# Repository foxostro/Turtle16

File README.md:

# Turtle16

Turtle16 is a sixteen-bit microcomputer built from discrete logic ICs and other simple parts. This repo contains the Kicad project, and other files necesary to build the hardware, as well as the simulator, assembler, and compiler.

## Computer Specifications

* Sixteen-bit homebrew CPU
* Five stage classic RISC pipeline, executing one instruction per clock cycle
* Eight general-purpose registers
* Operand forwarding to automatically resolve read-after-write hazards
* Pipeline stalls to automatically resolve other sorts of hazards
* No branch delay slots
* Primitive branch prediction, always predicting the branch is not taken

## Why did you do this?

I find computer architecture to be very interesting. Having already built a couple of homebrew breadboard computers in the style of the SAP-1, I wanted to do something more advanced. This an opportunity to learn how the classic five stage RISC pipeline works. While it would also be possible to build something like this in an FPGA, or even just an HDL simulator, I appreciate the physical reality of building an actual thing. At the same time, I've been learning so much about PCB layout, circuit design, circuit assembly and construction, and debugging, much of which seems broadly applicable to any electronics project.

Careful self-imposed limitations are important for a successful project. Limitation breeds creativity. For this project, the implementation of the CPU itself has been constrained to use only simple 7400-style parts. This means sticking to discrete logic and other medium-scale integration parts. Microprocessors and advanced FPGAs have been avoided. An exception has been made for primitive GALs as these fit the retro computer aesthetic.

For the computer's peripherals, I might relax these limitations in favor of getting something working. For example, I'm considering using an Arduino to interface with a PC. The sound hardware could be built around a retro-style audio IC such as one of the Yamaha OPL series chips or the Phillips SAA1099.

The danger of relaxing limitations is that it raises the question, why not go further? If I decide it's fine to implement graphics using a retro-style chip like the TMS9918A then why not use a Raspberry Pi, or the Gameduino 3X Dazzler? Why not simply implement the entire computer in an emulator running on a Raspberry Pi? Once placed in an enclosure, it won't look any different. The answer is that the project is not about the goal of building a working computer, or the goal of playing some games. This project is centered around learning how computers work.

## Getting Started

The simulator app can be used to simulate the computer and run example programs without having to build the hardware. The interactive debugger can be used to inspect the state of the computer. Several example saved simulator sessions are available in the TurtleTools/Examples/ directory. (At some point, I should add some better demoes. These are mostly just programs that I used in hardware verification.)

To run the simulator, open the TurtleTools Xcode project and run the Simulator16 scheme. Refer to the [Tool Chain](Documentation/TurtleTools.md) page for more details.

## Documentation

* [Architecture Overview](Documentation/Architecture.md)
* [Instruction Set Architecture](Documentation/ISA.md)
* [Programming](Documentation/Programming.md)
* [Tool Chain](Documentation/TurtleTools.md)
* [Bugs](Documentation/Bugs.md)
* [Future Work](Documentation/Future.md)

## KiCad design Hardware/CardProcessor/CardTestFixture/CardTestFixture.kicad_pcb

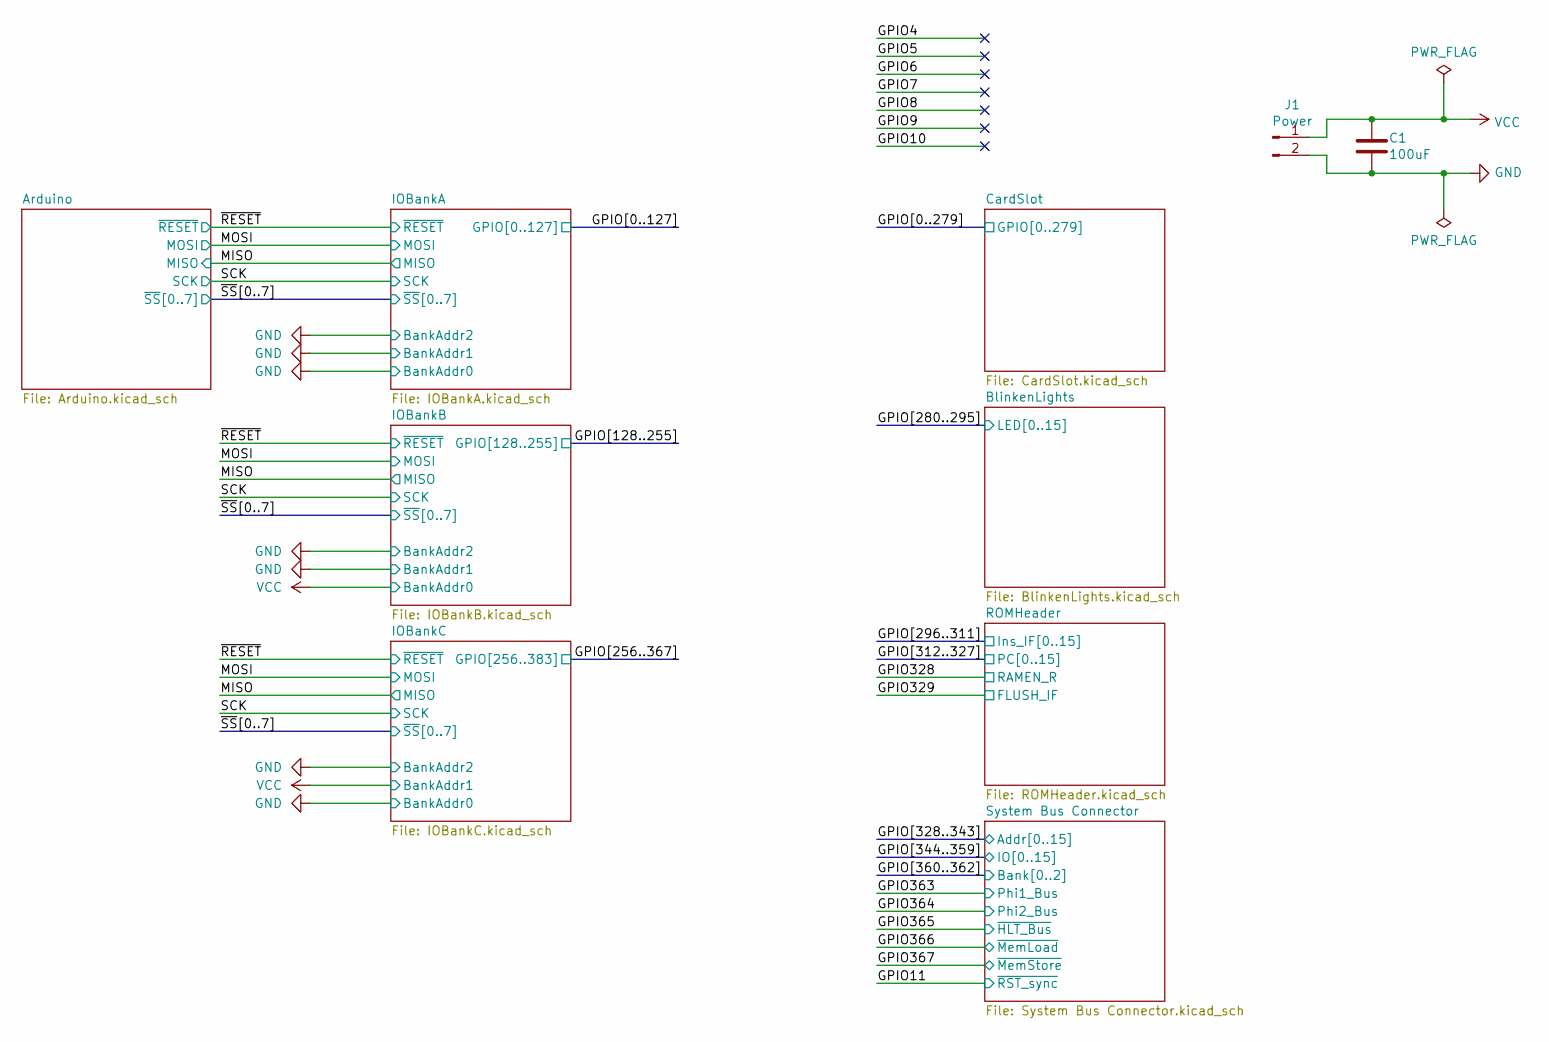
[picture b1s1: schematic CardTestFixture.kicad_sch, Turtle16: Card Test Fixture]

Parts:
C1: 100uF; C_1206_3216Metric; Manufacturer# AMK316ABJ107ML-T; Mouser# 963-AMK316ABJ107ML-T
J1: Power; 172448-0002; Manufacturer# 172448-0002; Mouser# 538-172448-0002

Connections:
GND: C1.2, J1.2; also elsewhere on the board
VCC: C1.1, J1.1; also elsewhere on the board

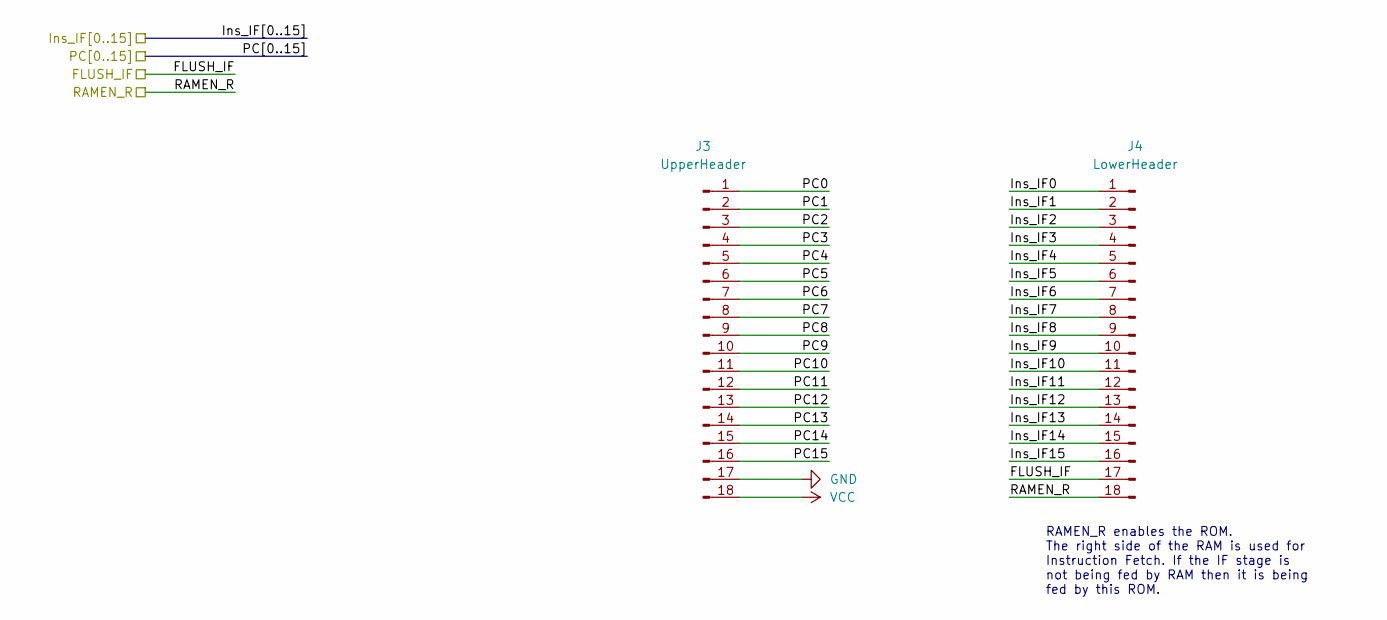
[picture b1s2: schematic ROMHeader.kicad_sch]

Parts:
J3: UpperHeader; PinHeader_1x18_P2.54mm_Vertical
J4: LowerHeader; PinHeader_1x18_P2.54mm_Vertical

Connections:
/GPIO296: J4.1; also elsewhere on the board
/GPIO297: J4.2; also elsewhere on the board
/GPIO298: J4.3; also elsewhere on the board
/GPIO299: J4.4; also elsewhere on the board
/GPIO300: J4.5; also elsewhere on the board
/GPIO301: J4.6; also elsewhere on the board
/GPIO302: J4.7; also elsewhere on the board
/GPIO303: J4.8; also elsewhere on the board
/GPIO304: J4.9; also elsewhere on the board
/GPIO305: J4.10; also elsewhere on the board
/GPIO306: J4.11; also elsewhere on the board
/GPIO307: J4.12; also elsewhere on the board
/GPIO308: J4.13; also elsewhere on the board
/GPIO309: J4.14; also elsewhere on the board
/GPIO310: J4.15; also elsewhere on the board
/GPIO311: J4.16; also elsewhere on the board
/GPIO312: J3.1; also elsewhere on the board
/GPIO313: J3.2; also elsewhere on the board
/GPIO314: J3.3; also elsewhere on the board
/GPIO315: J3.4; also elsewhere on the board
/GPIO316: J3.5; also elsewhere on the board
/GPIO317: J3.6; also elsewhere on the board
/GPIO318: J3.7; also elsewhere on the board
/GPIO319: J3.8; also elsewhere on the board
/GPIO320: J3.9; also elsewhere on the board
/GPIO321: J3.10; also elsewhere on the board
/GPIO322: J3.11; also elsewhere on the board
/GPIO323: J3.12; also elsewhere on the board
/GPIO324: J3.13; also elsewhere on the board
/GPIO325: J3.14; also elsewhere on the board
/GPIO326: J3.15; also elsewhere on the board
/GPIO327: J3.16; also elsewhere on the board
/GPIO328: J4.18; also elsewhere on the board
/GPIO329: J4.17; also elsewhere on the board
GND: J3.17; also elsewhere on the board
VCC: J3.18; also elsewhere on the board

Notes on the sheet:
RAMEN_R enables the ROM. The right side of the RAM is used for Instruction Fetch. If the IF stage is not being fed by RAM then it is being fed by this ROM.

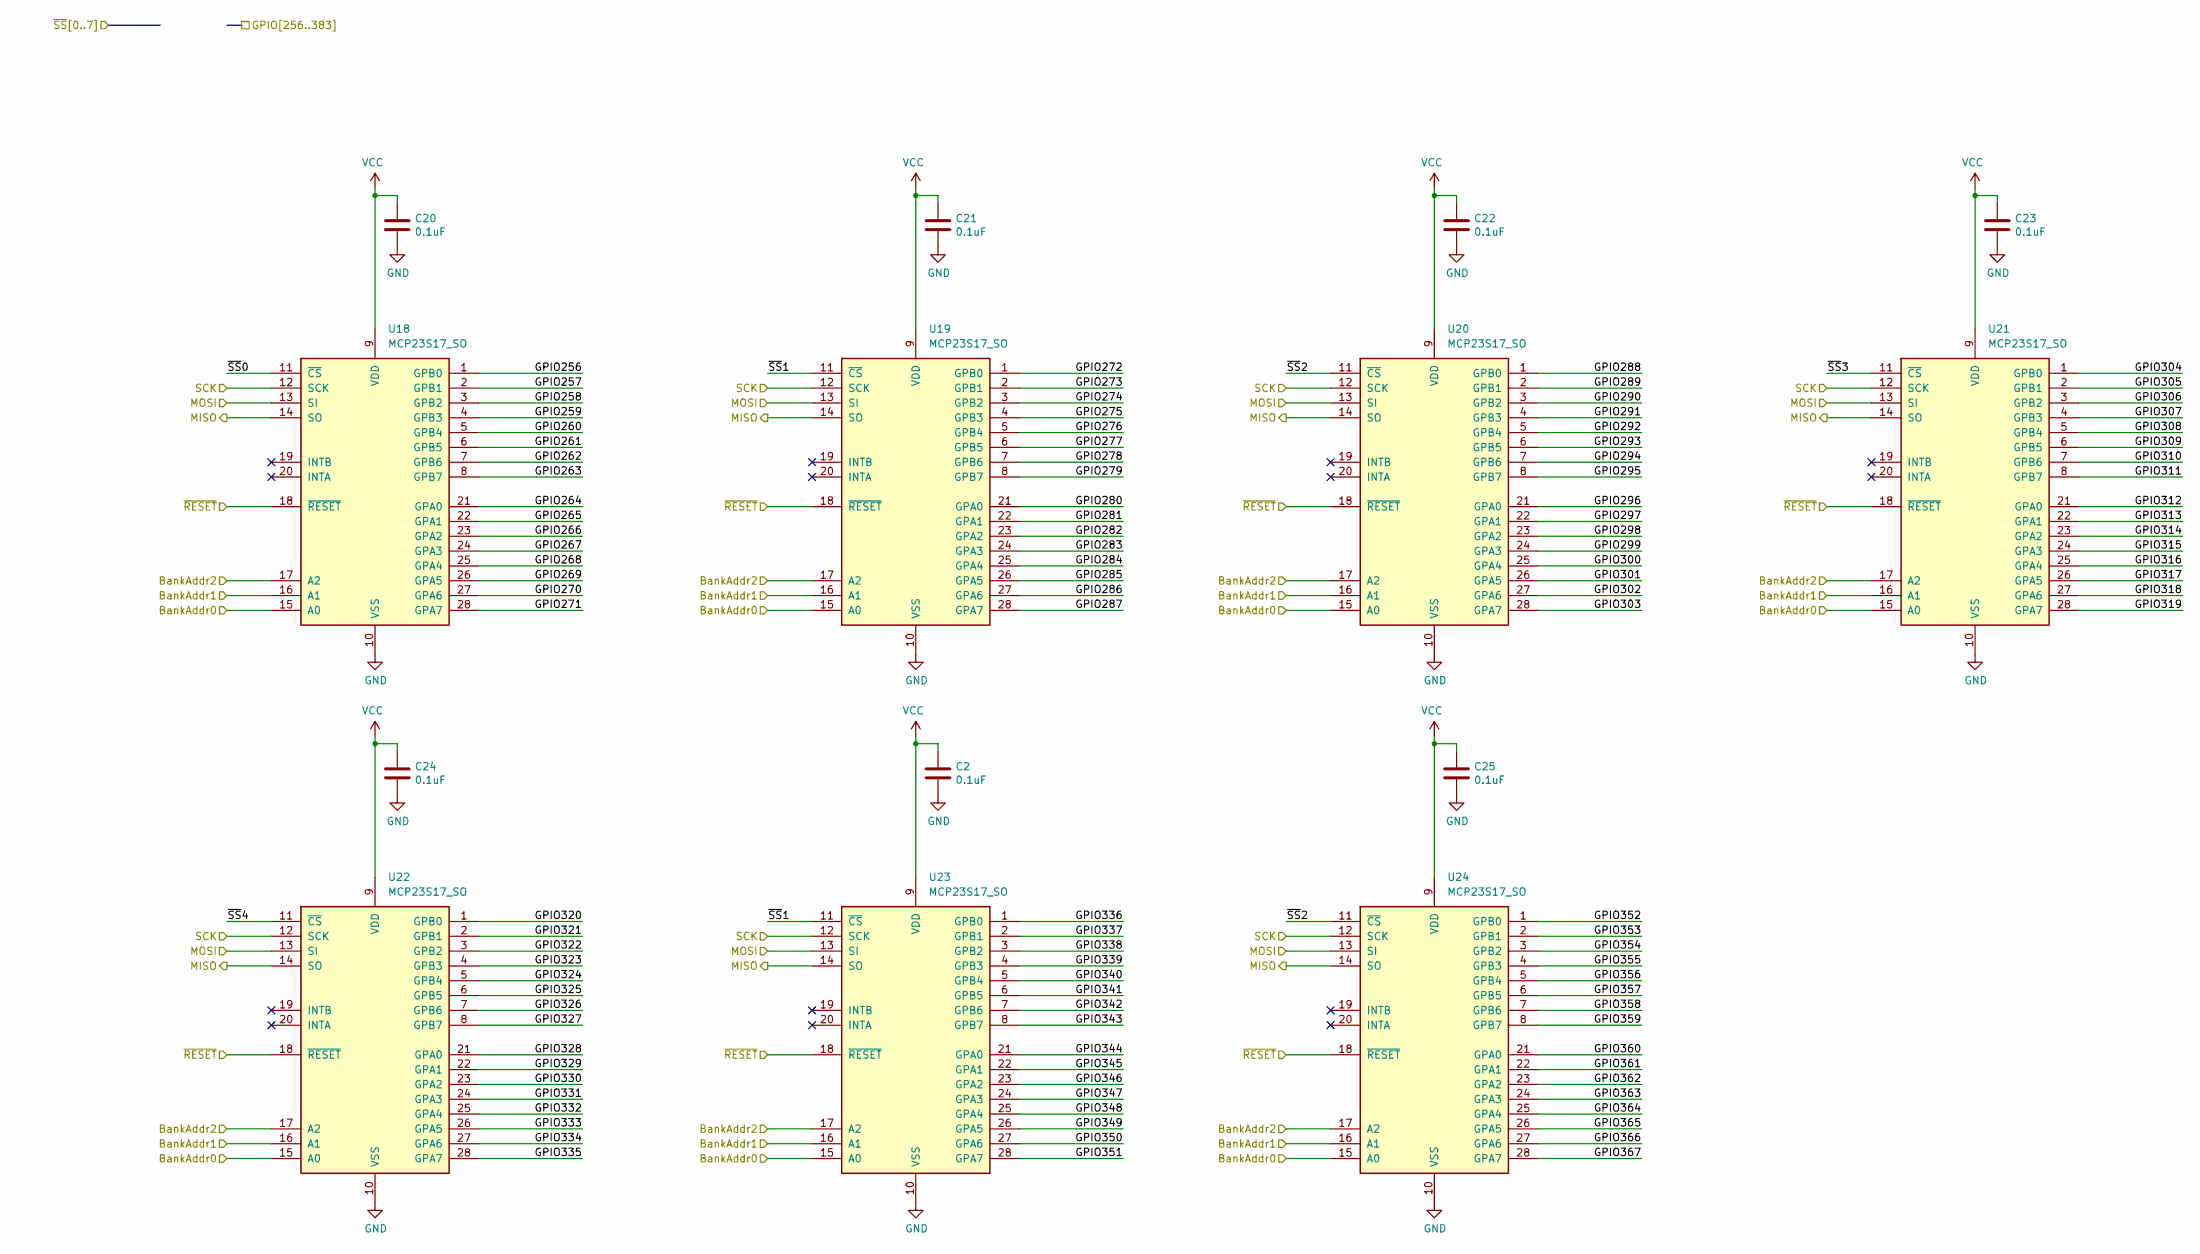
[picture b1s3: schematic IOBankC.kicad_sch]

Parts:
C2, C20, C21, C22, C23, C24, C25: 0.1uF; C_0603_1608Metric; Manufacturer# EMK107B7104KAHT; Mouser# 963-EMK107B7104KAHT
U18, U19, U20, U21, U22, U23, U24: MCP23S17_SO; SOIC-28W_7.5x17.9mm_P1.27mm

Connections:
/GPIO256: U18.1 (GPB0); also elsewhere on the board
/GPIO257: U18.2 (GPB1); also elsewhere on the board
/GPIO258: U18.3 (GPB2); also elsewhere on the board
/GPIO259: U18.4 (GPB3); also elsewhere on the board
/GPIO260: U18.5 (GPB4); also elsewhere on the board
/GPIO261: U18.6 (GPB5); also elsewhere on the board
/GPIO262: U18.7 (GPB6); also elsewhere on the board
/GPIO263: U18.8 (GPB7); also elsewhere on the board
/GPIO264: U18.21 (GPA0); also elsewhere on the board
/GPIO265: U18.22 (GPA1); also elsewhere on the board
/GPIO266: U18.23 (GPA2); also elsewhere on the board
/GPIO267: U18.24 (GPA3); also elsewhere on the board
/GPIO268: U18.25 (GPA4); also elsewhere on the board
/GPIO269: U18.26 (GPA5); also elsewhere on the board
/GPIO270: U18.27 (GPA6); also elsewhere on the board
/GPIO271: U18.28 (GPA7); also elsewhere on the board
/GPIO272: U19.1 (GPB0); also elsewhere on the board
/GPIO273: U19.2 (GPB1); also elsewhere on the board
/GPIO274: U19.3 (GPB2); also elsewhere on the board
/GPIO275: U19.4 (GPB3); also elsewhere on the board
/GPIO276: U19.5 (GPB4); also elsewhere on the board
/GPIO277: U19.6 (GPB5); also elsewhere on the board
/GPIO278: U19.7 (GPB6); also elsewhere on the board
/GPIO279: U19.8 (GPB7); also elsewhere on the board
/GPIO280: U19.21 (GPA0); also elsewhere on the board
/GPIO281: U19.22 (GPA1); also elsewhere on the board
/GPIO282: U19.23 (GPA2); also elsewhere on the board
/GPIO283: U19.24 (GPA3); also elsewhere on the board
/GPIO284: U19.25 (GPA4); also elsewhere on the board
/GPIO285: U19.26 (GPA5); also elsewhere on the board
/GPIO286: U19.27 (GPA6); also elsewhere on the board
/GPIO287: U19.28 (GPA7); also elsewhere on the board
/GPIO288: U20.1 (GPB0); also elsewhere on the board
/GPIO289: U20.2 (GPB1); also elsewhere on the board
/GPIO290: U20.3 (GPB2); also elsewhere on the board
/GPIO291: U20.4 (GPB3); also elsewhere on the board
/GPIO292: U20.5 (GPB4); also elsewhere on the board
/GPIO293: U20.6 (GPB5); also elsewhere on the board
/GPIO294: U20.7 (GPB6); also elsewhere on the board
/GPIO295: U20.8 (GPB7); also elsewhere on the board
/GPIO296: U20.21 (GPA0); also elsewhere on the board
/GPIO297: U20.22 (GPA1); also elsewhere on the board
/GPIO298: U20.23 (GPA2); also elsewhere on the board
/GPIO299: U20.24 (GPA3); also elsewhere on the board
/GPIO300: U20.25 (GPA4); also elsewhere on the board
/GPIO301: U20.26 (GPA5); also elsewhere on the board
/GPIO302: U20.27 (GPA6); also elsewhere on the board
/GPIO303: U20.28 (GPA7); also elsewhere on the board
/GPIO304: U21.1 (GPB0); also elsewhere on the board
/GPIO305: U21.2 (GPB1); also elsewhere on the board
/GPIO306: U21.3 (GPB2); also elsewhere on the board
/GPIO307: U21.4 (GPB3); also elsewhere on the board
/GPIO308: U21.5 (GPB4); also elsewhere on the board
/GPIO309: U21.6 (GPB5); also elsewhere on the board
/GPIO310: U21.7 (GPB6); also elsewhere on the board
/GPIO311: U21.8 (GPB7); also elsewhere on the board
/GPIO312: U21.21 (GPA0); also elsewhere on the board
/GPIO313: U21.22 (GPA1); also elsewhere on the board
/GPIO314: U21.23 (GPA2); also elsewhere on the board
/GPIO315: U21.24 (GPA3); also elsewhere on the board
/GPIO316: U21.25 (GPA4); also elsewhere on the board
/GPIO317: U21.26 (GPA5); also elsewhere on the board
/GPIO318: U21.27 (GPA6); also elsewhere on the board
/GPIO319: U21.28 (GPA7); also elsewhere on the board
/GPIO320: U22.1 (GPB0); also elsewhere on the board
/GPIO321: U22.2 (GPB1); also elsewhere on the board
/GPIO322: U22.3 (GPB2); also elsewhere on the board
/GPIO323: U22.4 (GPB3); also elsewhere on the board
/GPIO324: U22.5 (GPB4); also elsewhere on the board
/GPIO325: U22.6 (GPB5); also elsewhere on the board
/GPIO326: U22.7 (GPB6); also elsewhere on the board
/GPIO327: U22.8 (GPB7); also elsewhere on the board
/GPIO328: U22.21 (GPA0); also elsewhere on the board
/GPIO329: U22.22 (GPA1); also elsewhere on the board
/GPIO330: U22.23 (GPA2); also elsewhere on the board
/GPIO331: U22.24 (GPA3); also elsewhere on the board
/GPIO332: U22.25 (GPA4); also elsewhere on the board
/GPIO333: U22.26 (GPA5); also elsewhere on the board
/GPIO334: U22.27 (GPA6); also elsewhere on the board
/GPIO335: U22.28 (GPA7); also elsewhere on the board
/GPIO336: U23.1 (GPB0); also elsewhere on the board
/GPIO337: U23.2 (GPB1); also elsewhere on the board
/GPIO338: U23.3 (GPB2); also elsewhere on the board
/GPIO339: U23.4 (GPB3); also elsewhere on the board
/GPIO340: U23.5 (GPB4); also elsewhere on the board
/GPIO341: U23.6 (GPB5); also elsewhere on the board
/GPIO342: U23.7 (GPB6); also elsewhere on the board
/GPIO343: U23.8 (GPB7); also elsewhere on the board
/GPIO344: U23.21 (GPA0); also elsewhere on the board
/GPIO345: U23.22 (GPA1); also elsewhere on the board
/GPIO346: U23.23 (GPA2); also elsewhere on the board
/GPIO347: U23.24 (GPA3); also elsewhere on the board
/GPIO348: U23.25 (GPA4); also elsewhere on the board
/GPIO349: U23.26 (GPA5); also elsewhere on the board
/GPIO350: U23.27 (GPA6); also elsewhere on the board
/GPIO351: U23.28 (GPA7); also elsewhere on the board
/GPIO352: U24.1 (GPB0); also elsewhere on the board
/GPIO353: U24.2 (GPB1); also elsewhere on the board
/GPIO354: U24.3 (GPB2); also elsewhere on the board
/GPIO355: U24.4 (GPB3); also elsewhere on the board
/GPIO356: U24.5 (GPB4); also elsewhere on the board
/GPIO357: U24.6 (GPB5); also elsewhere on the board
/GPIO358: U24.7 (GPB6); also elsewhere on the board
/GPIO359: U24.8 (GPB7); also elsewhere on the board
/GPIO360: U24.21 (GPA0); also elsewhere on the board
/GPIO361: U24.22 (GPA1); also elsewhere on the board
/GPIO362: U24.23 (GPA2); also elsewhere on the board
/GPIO363: U24.24 (GPA3); also elsewhere on the board
/GPIO364: U24.25 (GPA4); also elsewhere on the board
/GPIO365: U24.26 (GPA5); also elsewhere on the board
/GPIO366: U24.27 (GPA6); also elsewhere on the board
/GPIO367: U24.28 (GPA7); also elsewhere on the board
/MISO: U18.14 (SO), U19.14 (SO), U20.14 (SO), U21.14 (SO), U22.14 (SO), U23.14 (SO), U24.14 (SO); also elsewhere on the board
/MOSI: U18.13 (SI), U19.13 (SI), U20.13 (SI), U21.13 (SI), U22.13 (SI), U23.13 (SI), U24.13 (SI); also elsewhere on the board
/SCK: U18.12 (SCK), U19.12 (SCK), U20.12 (SCK), U21.12 (SCK), U22.12 (SCK), U23.12 (SCK), U24.12 (SCK); also elsewhere on the board
/~RESET: U18.18 (~RESET), U19.18 (~RESET), U20.18 (~RESET), U21.18 (~RESET), U22.18 (~RESET), U23.18 (~RESET), U24.18 (~RESET); also elsewhere on the board
/~SS0: U18.11 (~CS); also elsewhere on the board
/~SS1: U19.11 (~CS), U23.11 (~CS); also elsewhere on the board
/~SS2: U20.11 (~CS), U24.11 (~CS); also elsewhere on the board
/~SS3: U21.11 (~CS); also elsewhere on the board
/~SS4: U22.11 (~CS); also elsewhere on the board
GND: C2.2, C20.2, C21.2, C22.2, C23.2, C24.2, C25.2, U18.10 (VSS), U18.15 (A0), U18.17 (A2), U19.10 (VSS), U19.15 (A0), U19.17 (A2), U20.10 (VSS), U20.15 (A0), U20.17 (A2), U21.10 (VSS), U21.15 (A0), U21.17 (A2), U22.10 (VSS), U22.15 (A0), U22.17 (A2), U23.10 (VSS), U23.15 (A0), U23.17 (A2), U24.10 (VSS), U24.15 (A0), U24.17 (A2); also elsewhere on the board
VCC: C2.1, C20.1, C21.1, C22.1, C23.1, C24.1, C25.1, U18.9 (VDD), U18.16 (A1), U19.9 (VDD), U19.16 (A1), U20.9 (VDD), U20.16 (A1), U21.9 (VDD), U21.16 (A1), U22.9 (VDD), U22.16 (A1), U23.9 (VDD), U23.16 (A1), U24.9 (VDD), U24.16 (A1); also elsewhere on the board

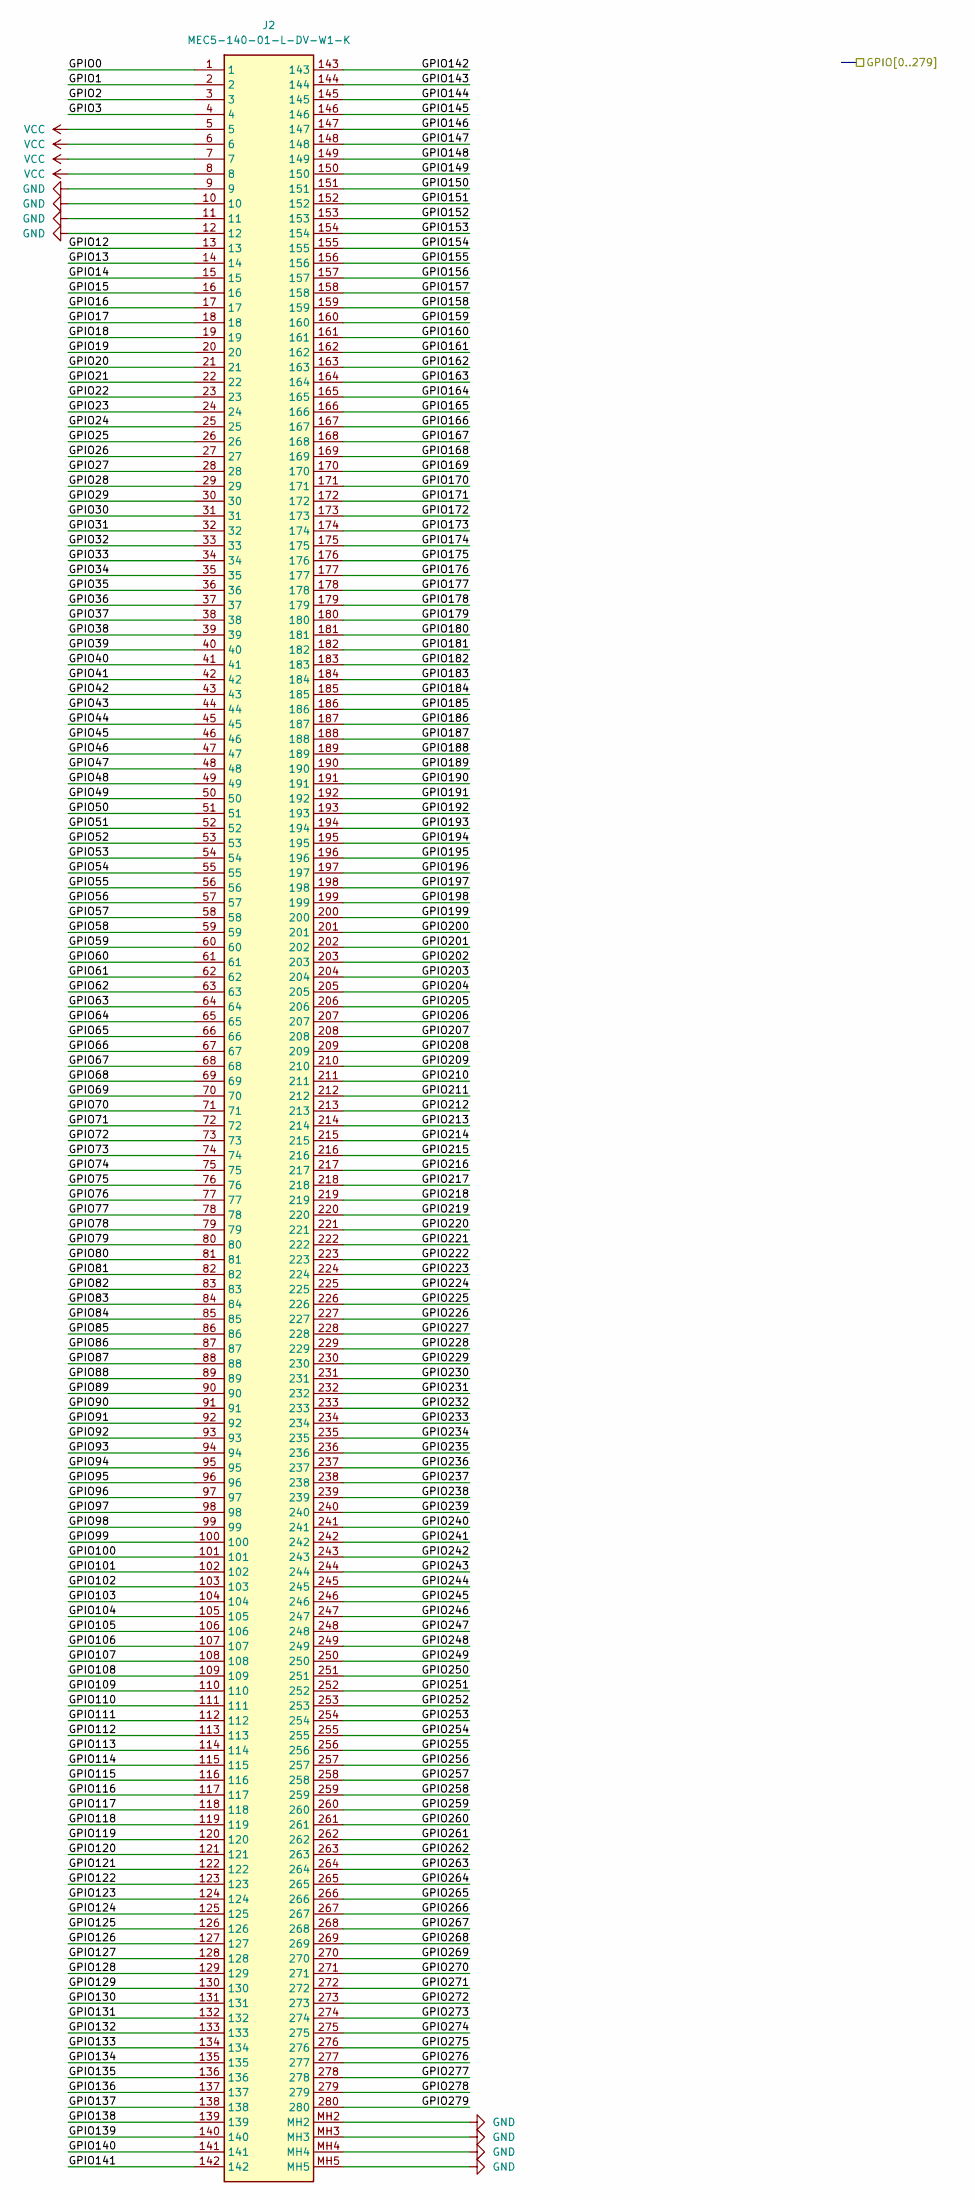
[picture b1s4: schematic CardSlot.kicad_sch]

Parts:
J2: MEC5-140-01-L-DV-W1-K; MEC514001LDVW1K; Mouser Part Number 200-MEC514001LDVW1K

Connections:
/GPIO0: J2.1; also elsewhere on the board
/GPIO1: J2.2; also elsewhere on the board
/GPIO2: J2.3; also elsewhere on the board
/GPIO3: J2.4; also elsewhere on the board
/GPIO12: J2.13; also elsewhere on the board
/GPIO13: J2.14; also elsewhere on the board
/GPIO14: J2.15; also elsewhere on the board
/GPIO15: J2.16; also elsewhere on the board
/GPIO16: J2.17; also elsewhere on the board
/GPIO17: J2.18; also elsewhere on the board
/GPIO18: J2.19; also elsewhere on the board
/GPIO19: J2.20; also elsewhere on the board
/GPIO20: J2.21; also elsewhere on the board
/GPIO21: J2.22; also elsewhere on the board
/GPIO22: J2.23; also elsewhere on the board
/GPIO23: J2.24; also elsewhere on the board
/GPIO24: J2.25; also elsewhere on the board
/GPIO25: J2.26; also elsewhere on the board
/GPIO26: J2.27; also elsewhere on the board
/GPIO27: J2.28; also elsewhere on the board
/GPIO28: J2.29; also elsewhere on the board
/GPIO29: J2.30; also elsewhere on the board
/GPIO30: J2.31; also elsewhere on the board
/GPIO31: J2.32; also elsewhere on the board
/GPIO32: J2.33; also elsewhere on the board
/GPIO33: J2.34; also elsewhere on the board
/GPIO34: J2.35; also elsewhere on the board
/GPIO35: J2.36; also elsewhere on the board
/GPIO36: J2.37; also elsewhere on the board
/GPIO37: J2.38; also elsewhere on the board
/GPIO38: J2.39; also elsewhere on the board
/GPIO39: J2.40; also elsewhere on the board
/GPIO40: J2.41; also elsewhere on the board
/GPIO41: J2.42; also elsewhere on the board
/GPIO42: J2.43; also elsewhere on the board
/GPIO43: J2.44; also elsewhere on the board
/GPIO44: J2.45; also elsewhere on the board
/GPIO45: J2.46; also elsewhere on the board
/GPIO46: J2.47; also elsewhere on the board
/GPIO47: J2.48; also elsewhere on the board
/GPIO48: J2.49; also elsewhere on the board
/GPIO49: J2.50; also elsewhere on the board
/GPIO50: J2.51; also elsewhere on the board
/GPIO51: J2.52; also elsewhere on the board
/GPIO52: J2.53; also elsewhere on the board
/GPIO53: J2.54; also elsewhere on the board
/GPIO54: J2.55; also elsewhere on the board
/GPIO55: J2.56; also elsewhere on the board
/GPIO56: J2.57; also elsewhere on the board
/GPIO57: J2.58; also elsewhere on the board
/GPIO58: J2.59; also elsewhere on the board
/GPIO59: J2.60; also elsewhere on the board
/GPIO60: J2.61; also elsewhere on the board
/GPIO61: J2.62; also elsewhere on the board
/GPIO62: J2.63; also elsewhere on the board
/GPIO63: J2.64; also elsewhere on the board
/GPIO64: J2.65; also elsewhere on the board
/GPIO65: J2.66; also elsewhere on the board
/GPIO66: J2.67; also elsewhere on the board
/GPIO67: J2.68; also elsewhere on the board
/GPIO68: J2.69; also elsewhere on the board
/GPIO69: J2.70; also elsewhere on the board
/GPIO70: J2.71; also elsewhere on the board
/GPIO71: J2.72; also elsewhere on the board
/GPIO72: J2.73; also elsewhere on the board
/GPIO73: J2.74; also elsewhere on the board
/GPIO74: J2.75; also elsewhere on the board
/GPIO75: J2.76; also elsewhere on the board
/GPIO76: J2.77; also elsewhere on the board
/GPIO77: J2.78; also elsewhere on the board
/GPIO78: J2.79; also elsewhere on the board
/GPIO79: J2.80; also elsewhere on the board
/GPIO80: J2.81; also elsewhere on the board
/GPIO81: J2.82; also elsewhere on the board
/GPIO82: J2.83; also elsewhere on the board
/GPIO83: J2.84; also elsewhere on the board
/GPIO84: J2.85; also elsewhere on the board
/GPIO85: J2.86; also elsewhere on the board
/GPIO86: J2.87; also elsewhere on the board
/GPIO87: J2.88; also elsewhere on the board
/GPIO88: J2.89; also elsewhere on the board
/GPIO89: J2.90; also elsewhere on the board
/GPIO90: J2.91; also elsewhere on the board
/GPIO91: J2.92; also elsewhere on the board
/GPIO92: J2.93; also elsewhere on the board
/GPIO93: J2.94; also elsewhere on the board
/GPIO94: J2.95; also elsewhere on the board
/GPIO95: J2.96; also elsewhere on the board
/GPIO96: J2.97; also elsewhere on the board
/GPIO97: J2.98; also elsewhere on the board
/GPIO98: J2.99; also elsewhere on the board
/GPIO99: J2.100; also elsewhere on the board
/GPIO100: J2.101; also elsewhere on the board
/GPIO101: J2.102; also elsewhere on the board
/GPIO102: J2.103; also elsewhere on the board
/GPIO103: J2.104; also elsewhere on the board
/GPIO104: J2.105; also elsewhere on the board
/GPIO105: J2.106; also elsewhere on the board
/GPIO106: J2.107; also elsewhere on the board
/GPIO107: J2.108; also elsewhere on the board
/GPIO108: J2.109; also elsewhere on the board
/GPIO109: J2.110; also elsewhere on the board
/GPIO110: J2.111; also elsewhere on the board
/GPIO111: J2.112; also elsewhere on the board
/GPIO112: J2.113; also elsewhere on the board
/GPIO113: J2.114; also elsewhere on the board
/GPIO114: J2.115; also elsewhere on the board
/GPIO115: J2.116; also elsewhere on the board
/GPIO116: J2.117; also elsewhere on the board
/GPIO117: J2.118; also elsewhere on the board
/GPIO118: J2.119; also elsewhere on the board
/GPIO119: J2.120; also elsewhere on the board
/GPIO120: J2.121; also elsewhere on the board
/GPIO121: J2.122; also elsewhere on the board
/GPIO122: J2.123; also elsewhere on the board
/GPIO123: J2.124; also elsewhere on the board
/GPIO124: J2.125; also elsewhere on the board
/GPIO125: J2.126; also elsewhere on the board
/GPIO126: J2.127; also elsewhere on the board
/GPIO127: J2.128; also elsewhere on the board
/GPIO128: J2.129; also elsewhere on the board
/GPIO129: J2.130; also elsewhere on the board
/GPIO130: J2.131; also elsewhere on the board
/GPIO131: J2.132; also elsewhere on the board
/GPIO132: J2.133; also elsewhere on the board
/GPIO133: J2.134; also elsewhere on the board
/GPIO134: J2.135; also elsewhere on the board
/GPIO135: J2.136; also elsewhere on the board
/GPIO136: J2.137; also elsewhere on the board
/GPIO137: J2.138; also elsewhere on the board
/GPIO138: J2.139; also elsewhere on the board
/GPIO139: J2.140; also elsewhere on the board
/GPIO140: J2.141; also elsewhere on the board
/GPIO141: J2.142; also elsewhere on the board
/GPIO142: J2.143; also elsewhere on the board
/GPIO143: J2.144; also elsewhere on the board
/GPIO144: J2.145; also elsewhere on the board
/GPIO145: J2.146; also elsewhere on the board
/GPIO146: J2.147; also elsewhere on the board
/GPIO147: J2.148; also elsewhere on the board
/GPIO148: J2.149; also elsewhere on the board
/GPIO149: J2.150; also elsewhere on the board
/GPIO150: J2.151; also elsewhere on the board
/GPIO151: J2.152; also elsewhere on the board
/GPIO152: J2.153; also elsewhere on the board
/GPIO153: J2.154; also elsewhere on the board
/GPIO154: J2.155; also elsewhere on the board
/GPIO155: J2.156; also elsewhere on the board
/GPIO156: J2.157; also elsewhere on the board
/GPIO157: J2.158; also elsewhere on the board
/GPIO158: J2.159; also elsewhere on the board
/GPIO159: J2.160; also elsewhere on the board
/GPIO160: J2.161; also elsewhere on the board
/GPIO161: J2.162; also elsewhere on the board
/GPIO162: J2.163; also elsewhere on the board
/GPIO163: J2.164; also elsewhere on the board
/GPIO164: J2.165; also elsewhere on the board
/GPIO165: J2.166; also elsewhere on the board
/GPIO166: J2.167; also elsewhere on the board
/GPIO167: J2.168; also elsewhere on the board
/GPIO168: J2.169; also elsewhere on the board
/GPIO169: J2.170; also elsewhere on the board
/GPIO170: J2.171; also elsewhere on the board
/GPIO171: J2.172; also elsewhere on the board
/GPIO172: J2.173; also elsewhere on the board
/GPIO173: J2.174; also elsewhere on the board
/GPIO174: J2.175; also elsewhere on the board
/GPIO175: J2.176; also elsewhere on the board
/GPIO176: J2.177; also elsewhere on the board
/GPIO177: J2.178; also elsewhere on the board
/GPIO178: J2.179; also elsewhere on the board
/GPIO179: J2.180; also elsewhere on the board
/GPIO180: J2.181; also elsewhere on the board
/GPIO181: J2.182; also elsewhere on the board
/GPIO182: J2.183; also elsewhere on the board
/GPIO183: J2.184; also elsewhere on the board
/GPIO184: J2.185; also elsewhere on the board
/GPIO185: J2.186; also elsewhere on the board
/GPIO186: J2.187; also elsewhere on the board
/GPIO187: J2.188; also elsewhere on the board
/GPIO188: J2.189; also elsewhere on the board
/GPIO189: J2.190; also elsewhere on the board
/GPIO190: J2.191; also elsewhere on the board
/GPIO191: J2.192; also elsewhere on the board
/GPIO192: J2.193; also elsewhere on the board
/GPIO193: J2.194; also elsewhere on the board
/GPIO194: J2.195; also elsewhere on the board
/GPIO195: J2.196; also elsewhere on the board
/GPIO196: J2.197; also elsewhere on the board
/GPIO197: J2.198; also elsewhere on the board
/GPIO198: J2.199; also elsewhere on the board
/GPIO199: J2.200; also elsewhere on the board
/GPIO200: J2.201; also elsewhere on the board
/GPIO201: J2.202; also elsewhere on the board
/GPIO202: J2.203; also elsewhere on the board
/GPIO203: J2.204; also elsewhere on the board
/GPIO204: J2.205; also elsewhere on the board
/GPIO205: J2.206; also elsewhere on the board
/GPIO206: J2.207; also elsewhere on the board
/GPIO207: J2.208; also elsewhere on the board
/GPIO208: J2.209; also elsewhere on the board
/GPIO209: J2.210; also elsewhere on the board
/GPIO210: J2.211; also elsewhere on the board
/GPIO211: J2.212; also elsewhere on the board
/GPIO212: J2.213; also elsewhere on the board
/GPIO213: J2.214; also elsewhere on the board
/GPIO214: J2.215; also elsewhere on the board
/GPIO215: J2.216; also elsewhere on the board
/GPIO216: J2.217; also elsewhere on the board
/GPIO217: J2.218; also elsewhere on the board
/GPIO218: J2.219; also elsewhere on the board
/GPIO219: J2.220; also elsewhere on the board
/GPIO220: J2.221; also elsewhere on the board
/GPIO221: J2.222; also elsewhere on the board
/GPIO222: J2.223; also elsewhere on the board
/GPIO223: J2.224; also elsewhere on the board
/GPIO224: J2.225; also elsewhere on the board
/GPIO225: J2.226; also elsewhere on the board
/GPIO226: J2.227; also elsewhere on the board
/GPIO227: J2.228; also elsewhere on the board
/GPIO228: J2.229; also elsewhere on the board
/GPIO229: J2.230; also elsewhere on the board
/GPIO230: J2.231; also elsewhere on the board
/GPIO231: J2.232; also elsewhere on the board
/GPIO232: J2.233; also elsewhere on the board
/GPIO233: J2.234; also elsewhere on the board
/GPIO234: J2.235; also elsewhere on the board
/GPIO235: J2.236; also elsewhere on the board
/GPIO236: J2.237; also elsewhere on the board
/GPIO237: J2.238; also elsewhere on the board
/GPIO238: J2.239; also elsewhere on the board
/GPIO239: J2.240; also elsewhere on the board
/GPIO240: J2.241; also elsewhere on the board
/GPIO241: J2.242; also elsewhere on the board
/GPIO242: J2.243; also elsewhere on the board
/GPIO243: J2.244; also elsewhere on the board
/GPIO244: J2.245; also elsewhere on the board
/GPIO245: J2.246; also elsewhere on the board
/GPIO246: J2.247; also elsewhere on the board
/GPIO247: J2.248; also elsewhere on the board
/GPIO248: J2.249; also elsewhere on the board
/GPIO249: J2.250; also elsewhere on the board
/GPIO250: J2.251; also elsewhere on the board
/GPIO251: J2.252; also elsewhere on the board
/GPIO252: J2.253; also elsewhere on the board
/GPIO253: J2.254; also elsewhere on the board
/GPIO254: J2.255; also elsewhere on the board
/GPIO255: J2.256; also elsewhere on the board
/GPIO256: J2.257; also elsewhere on the board
/GPIO257: J2.258; also elsewhere on the board
/GPIO258: J2.259; also elsewhere on the board
/GPIO259: J2.260; also elsewhere on the board
/GPIO260: J2.261; also elsewhere on the board
/GPIO261: J2.262; also elsewhere on the board
/GPIO262: J2.263; also elsewhere on the board
/GPIO263: J2.264; also elsewhere on the board
/GPIO264: J2.265; also elsewhere on the board
/GPIO265: J2.266; also elsewhere on the board
/GPIO266: J2.267; also elsewhere on the board
/GPIO267: J2.268; also elsewhere on the board
/GPIO268: J2.269; also elsewhere on the board
/GPIO269: J2.270; also elsewhere on the board
/GPIO270: J2.271; also elsewhere on the board
/GPIO271: J2.272; also elsewhere on the board
/GPIO272: J2.273; also elsewhere on the board
/GPIO273: J2.274; also elsewhere on the board
/GPIO274: J2.275; also elsewhere on the board
/GPIO275: J2.276; also elsewhere on the board
/GPIO276: J2.277; also elsewhere on the board
/GPIO277: J2.278; also elsewhere on the board
/GPIO278: J2.279; also elsewhere on the board
/GPIO279: J2.280; also elsewhere on the board
GND: J2.9, J2.10, J2.11, J2.12, J2.MH2, J2.MH3, J2.MH4, J2.MH5; also elsewhere on the board
VCC: J2.5, J2.6, J2.7, J2.8; also elsewhere on the board

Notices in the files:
Hardware/CardProcessor/BypassCard/BypassCard.kicad_pcb:
Copyright © 2025 Andrew Fox
